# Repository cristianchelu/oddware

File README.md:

# oddware

Personal collection of projects that don't deserve their own repositories.

## Projects

| Path | Description |
|------|-------------|
| [esphome.pet-bowl-monitor/](esphome.pet-bowl-monitor/) | ESPHome cat water bowl monitor — scale, camera, IR, Home Assistant integration |
| [esphome.petkit-eversweet-3-pro/](esphome.petkit-eversweet-3-pro/) | Replacement ESPHome base for the PetKit Eversweet 3 Pro UVC fountain — weighs it, logs every drink to Home Assistant |
| [esphome.petlibro-plwf105/](esphome.petlibro-plwf105/) | ESPHome firmware for the PetLibro Dockstream PLWF105 fountain — gram-calibrated scale, drink logging, one-button device UX |
| [zigbee.cat-toy/](zigbee.cat-toy/) | Zigbee cat toys: flappy bird, flappy fish and rolling ball on one shared board. Scripted KiCad layout |

## Moved out

| Project | New home |
|---------|----------|
| xiaomi-feeder-iv2001 — open firmware for the Xiaomi Smart Pet Food Feeder 2 | moved to [cristianchelu/xiaomi-feeder-iv2001](https://github.com/cristianchelu/xiaomi-feeder-iv2001) |

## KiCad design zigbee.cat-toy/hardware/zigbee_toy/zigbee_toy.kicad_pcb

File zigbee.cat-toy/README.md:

# @oddware/zigbee.cat-toy

One controller board for three battery-powered Zigbee cat toys: a flapping
bird, a flapping fish and a rolling ball. The board drives a motor and a
speaker, wakes on motion, charges over USB-C, and joins Home Assistant as a
sleepy Zigbee end device. The toys differ only in what is plugged into its
three connectors.

> This one is vibe coded: AI agents did most of the work, with me steering.
> It has never been built. There is no expectation that it works or will be
> finished; it's a side project parked here.

## Status

- **Rev A** — nRF52840 (Ebyte E73). Never built: the module and the
  accelerometer are "Standard only" parts at JLC, which put 5 assembled
  boards at about $200. Kept under the `zigbee.cat-toy/rev-a` tag.
- **Rev B** (this tree) — ESP32-C6. Every assembled part is eligible for
  JLC Economic PCBA. DRC-clean, not ordered yet.
- No firmware yet.
- Every fix from the [datasheet review](docs/design_review_rev_b.md) is in
  this tree.

## The toys

| Toy | Motor | Battery | Speaker |
|-----|-------|---------|---------|
| Flappy bird | N20 gearmotor, 6 V winding, 300–400 rpm | 1S LiPo pouch, ~500 mAh | yes |
| Flappy fish | same as bird | same as bird | no |
| Rolling ball | N20 gearmotor, 6 V winding, ~100 rpm | 803040, 1000 mAh | no |

- Any 3.7 V cell with a JST-PH lead works, protected or not. The board has
  its own protection and a reverse-polarity FET; JST-PH pigtails come wired
  both ways.
- Motor and speaker plug in with JST-SH (1 mm, 1 A per pin). Crimp the
  leads or buy SH pigtails.
- Keep the ceramic capacitor across the motor tabs. It suppresses brush noise
  next to a 2.4 GHz radio.
- The module has no antenna of its own. Plug a 2.4 GHz FPC antenna into its
  u.FL socket and stick it to the inside of the toy, away from the motor and
  the cell.

Printed parts for the ball and a bench pod:
[hardware/mech/README.md](hardware/mech/README.md).

## The board

36 × 23 mm, 2 layers, every assembled part on top. Passives are 0402,
bulk capacitors 0603/0805.

| Block | Part | Notes |
|-------|------|-------|
| MCU + radio | Espressif ESP32-C6-MINI-1U-H4 | Zigbee/Thread, BLE, Wi-Fi, u.FL antenna socket. USB Serial/JTAG on the charging port |
| 3.3 V | Richtek RT9080-33 | 2 µA quiescent, 600 mA |
| Motor driver | TI DRV8213 | Current sense on IPROPI, no shunt. Firmware picks the hardware current limit per toy: 1.66 A, 324 mA or 69 mA |
| Accelerometer | MSKSEMI LIS2DW12TR-MS | Wake-on-motion and tap. Not ST's LIS2DW12, see below |
| Charger | TP4054 | 260 mA from USB-C. Charge state goes to the MCU through a 10 k pull-up |
| Cell protection | XySemi XB5353A | Low side, FETs built in |
| Reverse polarity | AO3401A | High side |
| Speaker | AO3400A | Low-side PWM switch |
| Status LED | red 0603 | On a GPIO |
| USB ESD | ST USBLC6-2SC6 | D+/D− clamps, referenced to 3V3: on VBUS, the C6's D+ pull-up would back-feed VBUS while unplugged |
| Button | Alps SKRTLAE010 | Side push. Pairing, and BOOT for flashing |

- Left edge — motor and speaker JST-SH connectors (SMD, assembled), battery
  JST-PH (through-hole, hand-soldered).
- Right edge — USB-C and the side-push button, status LED above the USB-C.
- Top edge — the module, 1 mm from the edge.
- Back — 21 labelled test pads, debug UART among them.

**The accelerometer is not an ST part.** MSKSEMI sells it as
"LIS2DW12TR-MS", but the pinout and register map are its own: WHO_AM_I
reads 0x11 and the registers follow the LIS2DH layout (CTRL_REG1 at 0x20,
OUT_X_L at 0x28, AOI1/CLICK blocks). Use a LIS2DH-style driver. Only INT1
is wired; route both wake and tap to it. Pad 4 is grounded: the pin table
says NC, but the datasheet's connection column says GND in every mode.

Schematic: [PDF](hardware/zigbee_toy/zigbee_toy_schematic.pdf). Datasheet review:
[docs/design_review_rev_b.md](docs/design_review_rev_b.md).

### Pin map

| Module pin | GPIO | Net | Notes |
|---|---|---|---|
| 5 | IO2 | MOT_IPROPI | ADC1_CH2. 0.51 V = current limit reached |
| 6 | IO3 | MOT_IN1 | DRV8213 IN1 |
| 9 | IO4 | MOT_IN2 | DRV8213 IN2 |
| 19 | IO14 | MOT_GAINSEL | drive low / drive high / input (Hi-Z) |
| 10 | IO5 | SPK_PWM | speaker FET gate |
| 12, 13 | IO0, IO1 | XTAL_32K | 32.768 kHz crystal for the light-sleep clock |
| 15 | IO6 | VBAT_SENSE | ADC1_CH6, VBAT / 2 |
| 16 | IO7 | ACC_INT1 | low-power GPIO: wakes from deep sleep too |
| 22 | IO8 | I2C_SDA | 4.7 k pull-up, which also holds the IO8 strap high |
| 24 | IO18 | I2C_SCL | 4.7 k pull-up. Accelerometer at 0x19 |
| 23 | IO9 | BTN | BOOT strap, 10 k pull-up (R5). Hold while resetting for download mode |
| 25 | IO19 | VBUS_SENSE | 0.61 × VBUS: high when plugged in, charging or full |
| 26 | IO20 | CHG_STAT | low while charging, 10 k pull-up (R10) |
| 29 | IO23 | LED_STATUS | high = on |
| 17, 18 | IO12, IO13 | USB D−, D+ | |
| 30, 31 | RXD0, TXD0 | DBG_RX, DBG_TX | test pads, 3.3 V |
| 8 | EN | EN | 10 k / 1 µF power-on delay, test pad |

Unconnected: IO15 (a strapping pin), IO21, IO22.

Motor drive: PWM between drive and brake. Forward IN1 = 1, IN2 = 1 − duty;
reverse IN2 = 1, IN1 = 1 − duty. Both pins need a PWM channel. Drive/coast
also spins the motor, but IPROPI reads zero while coasting, so current
sensing and stall detection stop working. The driver only auto-sleeps with
IN1 = IN2 = 0; brake keeps it awake, so park both inputs low before sleeping.

The JST-SH is rated 1 A per pin. Use the 324 mA limit (GAINSEL Hi-Z) as the
default; at 1.66 A a stalled motor overloads the connector.

### Power

Idle current is about 65 µA, nearly all of it the C6 in Zigbee light sleep
(about 54 µA, a forum figure, not measured here). The regulator, the
protection IC, the accelerometer and the battery divider add a few µA each.
That is 1.6 mAh a day. Ten minutes of flapping costs about 25 mAh, so a
500 mAh bird gets roughly three weeks per charge.

The battery divider is 1 M / 1 M. At that impedance the ADC's own input
current shifts the reading; calibrate it against a meter in firmware.

- Low battery — the XB5353A cuts off at 2.4 V, but the C6 browns out below
  about 3.4 V during radio bursts and reboots in a loop. Stop the radio and
  sleep at 3.4 V; the protection IC is the last line.
- First cell — the XB5353A may start in its off state when a cell is
  connected. Plug in USB once to wake it.
- Charge state — CHG_STAT low = charging; high with VBUS_SENSE high = done;
  high with VBUS_SENSE low = unplugged. With USB plugged in and the radio
  awake, the board draws through the charger, which then stays in its
  constant-voltage float and CHG_STAT stays low. Not an error.
- Charger heat — 0.34 W at 260 mA into a 3.7 V cell. On a warm day the
  TP4054 folds its current back.

### Layout

- **Edge distance:** every assembled part body is at least 1 mm from the
  board edge (see [Ordering](#ordering)). Exempt: the USB-C and the button
  on the right edge, the two JST-SH plugs on the left. The SH fronts sit
  0.5 mm in from the edge so their solder tabs keep 0.3 mm of copper
  clearance. `gen_pcb.py` refuses a placement that breaks the rule.
- **Module position:** 1 mm from the top edge. Under it, two rows of parts
  with a channel between them: crystal, accelerometer and USB protection in
  the first row, regulator and the battery divider in the second.
- **USB-C side:** the channel between the module's right pads and the
  receptacle pads is 2.1 mm wide. Only the two CC pull-downs live in it,
  standing vertical beside their pads. The VBUS divider sits above the
  receptacle, beside the top mounting hole, fed from the upper VBUS pad;
  VBUS_SENSE comes back to pin 25 on the back layer, under the module's
  right pad column.
- **Antenna keepout:** no copper on either layer between the module's top
  pads and the board edge. That is the area under an ESP32-C6-MINI-1's PCB
  antenna, so the MINI-1 fits the same pads. The keepout is a rule area in
  the module footprint, so DRC checks it.
- **USB D+/D−:** each USB-C pad pair is joined on the back layer through
  vias inside the receptacle. D+ passes left of the shell tab, D− right of
  it, into the USBLC6 below the receptacle. From there both run on the back
  layer under the module's bottom edge and come up through vias inside the
  pad ring at pins 17 and 18.
- **Under the USB-C:** no top-layer copper except the pad escapes. On the
  back, only the escape vias and the VBUS run, so the shell still ties into
  the ground pour.
- **Crystal:** no back-layer copper under it or its traces.
- The DSN export turns the last two into keepouts for the autorouter; hand
  routes are not checked against them.
- **Battery corner:** the protection IC body is 1.4 mm from the JST-PH
  housing and 0.7 mm outside the 4 mm circle an M2 screw head covers at
  H2; CELL_P goes round its ground pad on the far side, and the bulk
  capacitor sits to the right of that with its own ground via.
- **VBAT:** back layer from the battery FET up the left column to the
  driver, and along the bottom in a channel between the two rows of test
  pads to the regulator, the battery divider and the charger.
- **3V3:** regulator, 22 µF next to it, 10 µF and 100 nF at module pin 3.
- **Motor driver:** C3's ground pad drops straight onto the thermal pad,
  which has two vias to the back. Keep the back plane under the driver
  whole: with one trace under it, C3's return path was 15 mm long instead
  of 1.
- **Charger:** two ground vias under the TP4054, on its pin 2, which is its
  heat path. The VBAT lane dips below them.
- **Ground:** both layers poured. `gen_pcb.py stitch` adds a 2.5 mm via grid
  and a via to every pour island it can reach. Five of the module's nine
  centre ground pads have a via.

## Flashing

The C6 has USB Serial/JTAG on the charging port: flashing, console and
debugging over one cable.

1. Connect the USB-C to the computer.
2. Flash with ESPHome or esptool. The tool resets the C6 into download mode
   over USB; the button is not needed.

If the firmware has disabled USB or does not respond:

1. Hold the button.
2. Connect the EN test pad to a GND pad for a moment.
3. Release the button. The C6 is in download mode.

UART0 is also on the TX and RX test pads, 3.3 V.

## Rebuilding

The schematic and the board are generated by scripts. Do not edit them in
KiCad; the next build overwrites the changes.

| To change | Edit |
|-----------|------|
| Parts and nets | `hardware/tools/design.py` |
| Board placement | `hardware/tools/placement.py` |
| Copper | `hardware/tools/routes.py` (hand routes), `routes_frozen.py` (a frozen Freerouting pass, hand-edited since) |
| Silkscreen | `hardware/tools/silk.py` |

Needs the KiCad 10 flatpak, ImageMagick, and network access the first time
a new LCSC number shows up in the BOM.

1. Run `hardware/tools/build.sh`. It writes the schematic, runs ERC, checks
   the netlist against intent, and writes the PDF and the JLC BOM.
2. Run `hardware/tools/pcb_build.sh`. It places, adds the copper, stitches,
   adds the silkscreen, runs DRC and checks part spacing
   (`check_spacing.py`: bodies 0.2 mm, pads 0.15 mm apart; the library
   courtyards overlap by their margins). Placement fails if a part breaks the
   edge distance.
3. Run `hardware/tools/export_jlc.sh`. It writes `gerbers.zip`, `cpl.csv`
   and `bom.csv` to `hardware/zigbee_toy/build/jlc/`.

To autoroute nets that have no copper yet (needs the Freerouting flatpak and
a JDK; one pass takes up to 10 minutes):

1. Run `gen_pcb.py layout`, then `gen_pcb.py dsn`.
2. Run `tools/freerouting/Route.java` on `build/zigbee_toy.dsn`.
3. Run `gen_pcb.py ses`, then `freeze_routes.py append`. The new copper
   goes into `routes_frozen.py`.

Run the Python scripts with the flatpak's interpreter
(`flatpak run --command=python3 org.kicad.kicad`). Outputs go to `build/`
folders, which git ignores.

## Ordering

- Order Economic PCBA. Nine parts are JLC "Extended" ($3 each per order):
  module, motor driver, accelerometer, regulator, protection IC, USB ESD,
  USB-C, JST-SH, button. Parts come to about $8.25 a board.
- The order's BOM step decides Economic or Standard, not the "PCBA Type"
  field on the part page. One Standard-only part moves the whole order to
  Standard. Re-check there after any part swap.
- JLC flags the module and the accelerometer for X-ray inspection. Not
  confirmed yet whether that changes the PCBA type.
- Parts sit as close as 1 mm to the edge. JLC panelizes Economic boards
  itself and routes them apart, and its Economic FAQ asks for 0.3 mm. The
  2.5 mm in the general assembly terms is for Standard PCBA, where the
  machines grip the board's own edge.
- The USB-C overhangs the board edge by 1 mm. Say so in the order remark.
- JLC places a part using the origin and rotation of *its* EasyEDA
  footprint, not KiCad's. `jlc_cpl.py` fits each KiCad footprint onto the
  EasyEDA one and corrects the CPL (the module is 0.65 mm off, the USB-C
  1.6 mm); it fails if a fit is poor. Check JLC's 3D placement preview
  anyway. The EasyEDA footprints are cached in `hardware/tools/easyeda/`.
- The FPC antenna is not on the BOM. Any 2.4 GHz FPC antenna with a u.FL
  (IPEX MHF1) lead fits.
- The ESP32-C6-MINI-1 (PCB antenna) drops onto the same pads; its antenna
  overhangs the top edge by 3.1 mm. Swap the LCSC number in `design.py` and
  mention the overhang in the order remark. As of 2026-10 every MINI-1
  listing at JLC is out of stock and Standard only.

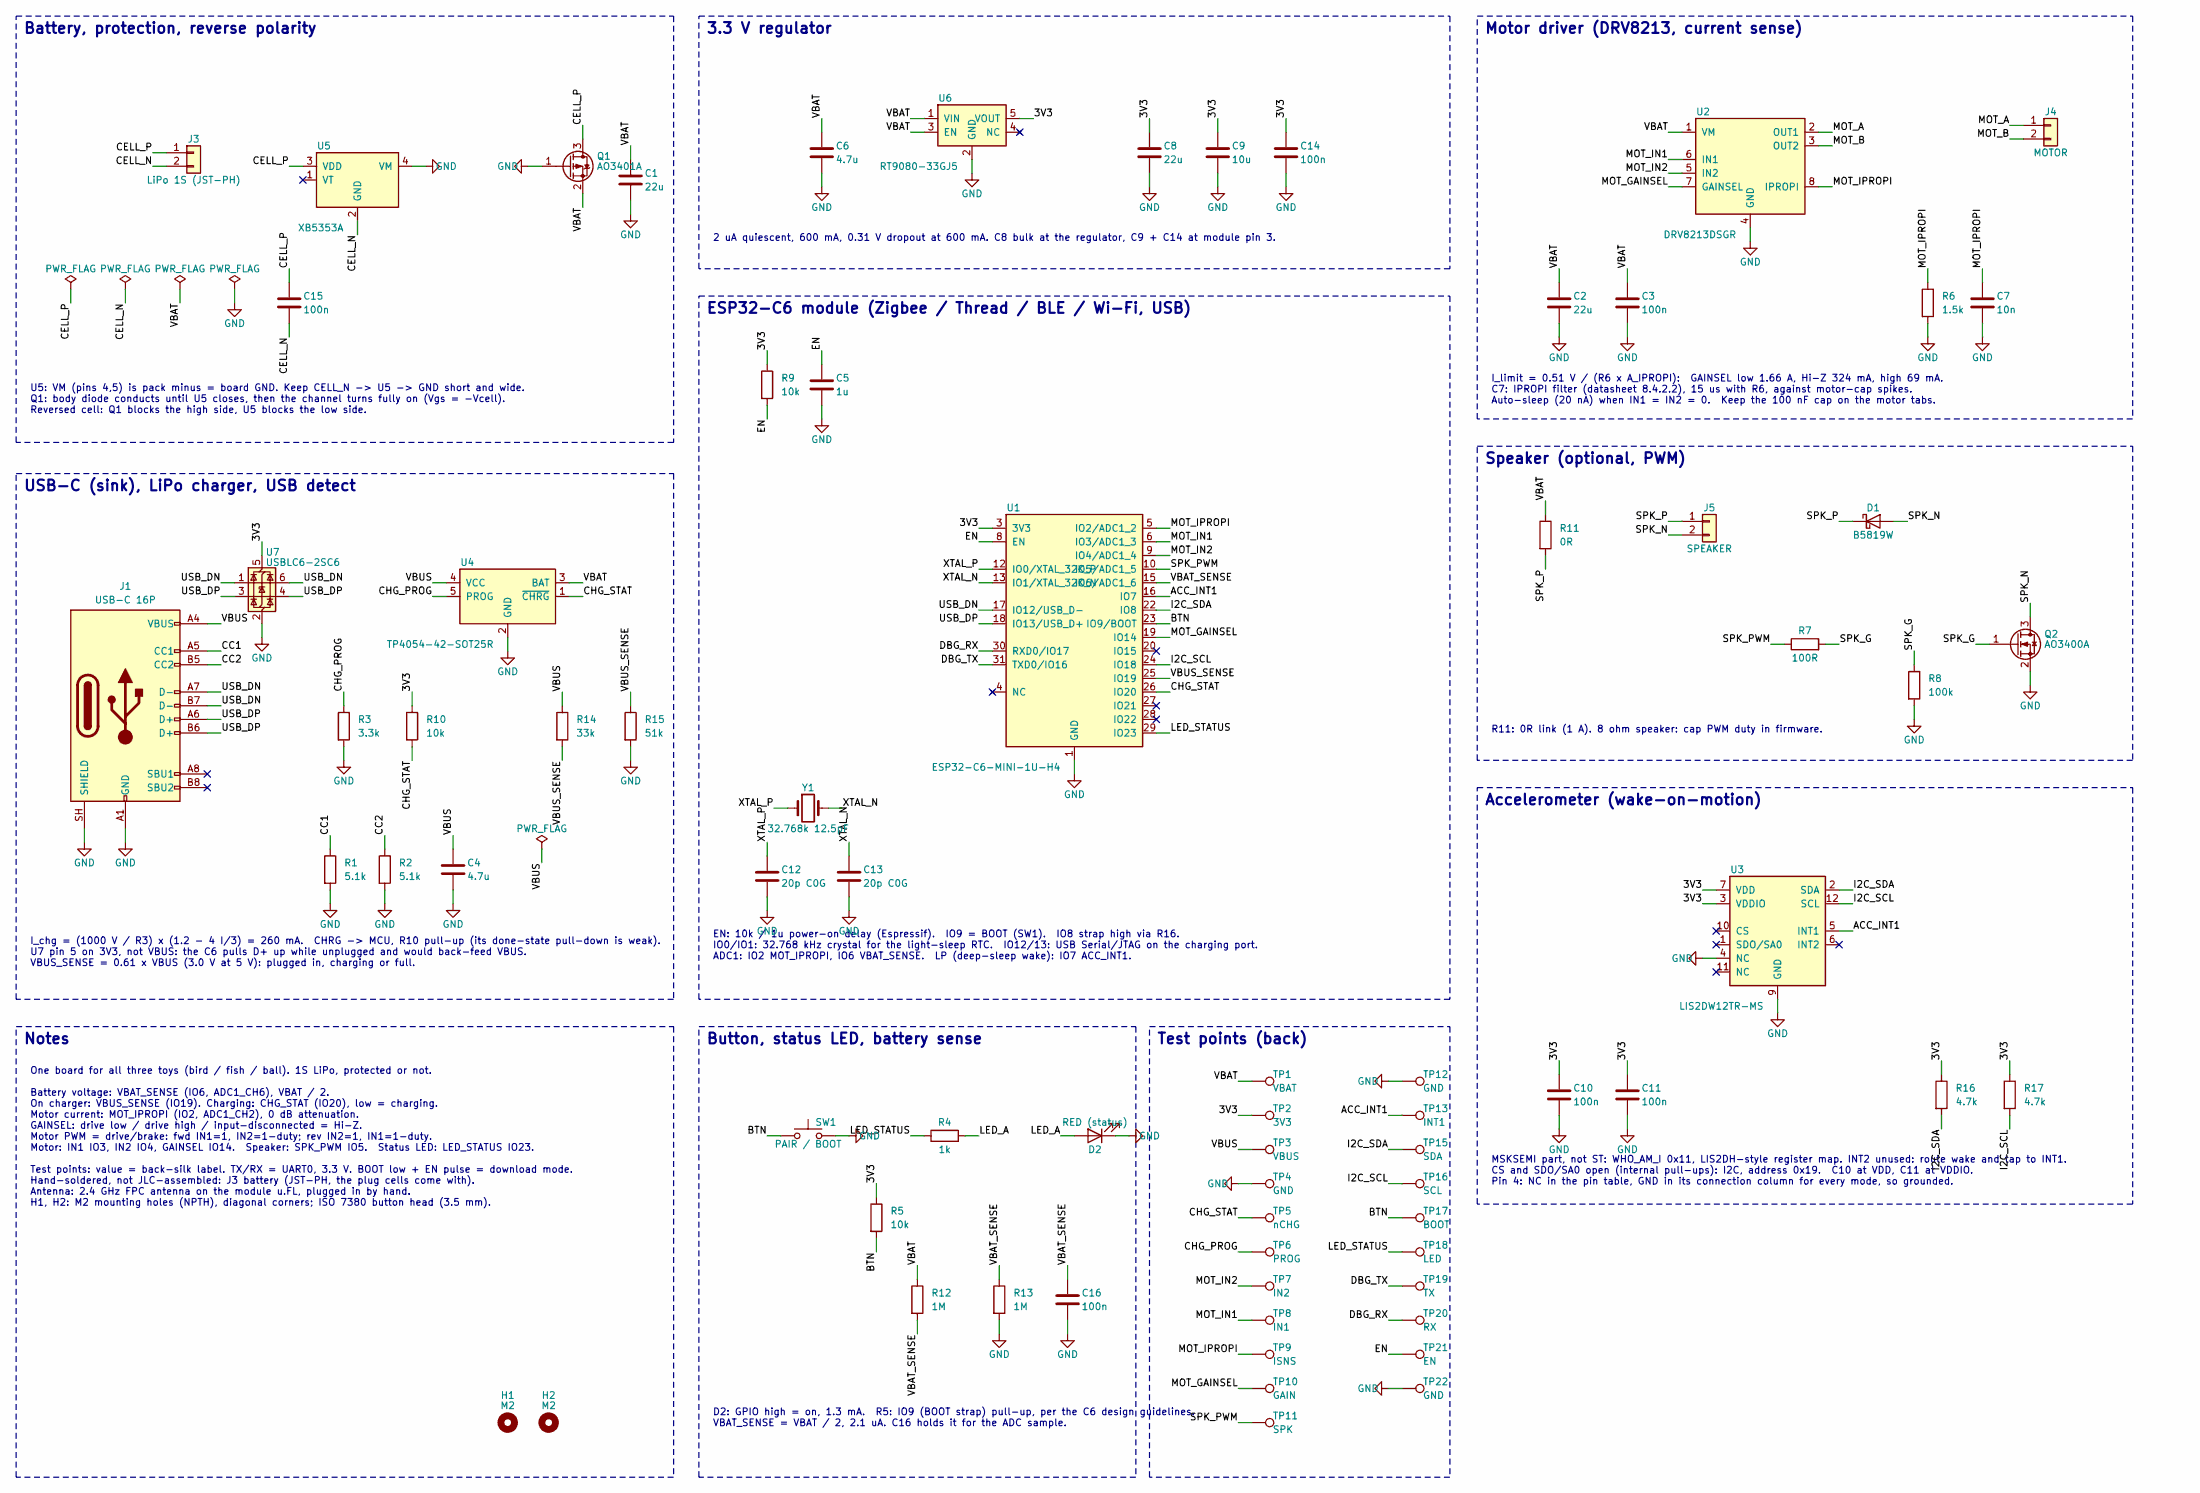
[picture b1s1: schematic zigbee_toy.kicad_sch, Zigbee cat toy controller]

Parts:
C1, C2, C8: 22u; C_0805_2012Metric; LCSC C45783
C3, C10, C11, C14, C15, C16: 100n; C_0402_1005Metric; LCSC C1525
C4, C6: 4.7u; C_0603_1608Metric; LCSC C19666
C5: 1u; C_0402_1005Metric; LCSC C52923
C7: 10n; C_0402_1005Metric; LCSC C15195
C9: 10u; C_0603_1608Metric; LCSC C19702
C12, C13: 20p C0G; C_0402_1005Metric; LCSC C1554
D1: B5819W; D_SOD-123; LCSC C8598
D2: RED (status); LED_0603_1608Metric; LCSC C2286
H1, H2: M2; MountingHole_2.2mm_M2_ISO7380
J1: USB-C 16P; USB_C_Receptacle_HRO_TYPE-C-31-M-12; LCSC C165948
J3: LiPo 1S (JST-PH); JST_PH_S2B-PH-K_1x02_P2.00mm_Horizontal; LCSC C173752
J4: MOTOR; JST_SH_SM02B-SRSS-TB_1x02-1MP_P1.00mm_Horizontal; LCSC C160402
J5: SPEAKER; JST_SH_SM02B-SRSS-TB_1x02-1MP_P1.00mm_Horizontal; LCSC C160402
Q1: AO3401A; SOT-23; LCSC C15127
Q2: AO3400A; SOT-23; LCSC C20917
R1, R2: 5.1k; R_0402_1005Metric; LCSC C25905
R3: 3.3k; R_0402_1005Metric; LCSC C25890
R4: 1k; R_0402_1005Metric; LCSC C11702
R5, R9, R10: 10k; R_0402_1005Metric; LCSC C25744
R6: 1.5k; R_0402_1005Metric; LCSC C25867
R7: 100R; R_0402_1005Metric; LCSC C25076
R8: 100k; R_0402_1005Metric; LCSC C25741
R11: 0R; R_0402_1005Metric; LCSC C17168
R12, R13: 1M; R_0402_1005Metric; LCSC C26083
R14: 33k; R_0402_1005Metric; LCSC C25779
R15: 51k; R_0402_1005Metric; LCSC C25794
R16, R17: 4.7k; R_0402_1005Metric; LCSC C25900
SW1: PAIR / BOOT; SW_Push_1P1T-MP_NO_Horizontal_Alps_SKRTLAE010; LCSC C110293
TP1: VBAT; TestPoint_Pad_D1.0mm
TP2: 3V3; TestPoint_Pad_D1.0mm
TP3: VBUS; TestPoint_Pad_D1.0mm
TP4, TP12, TP22: GND; TestPoint_Pad_D1.0mm
TP5: nCHG; TestPoint_Pad_D1.0mm
TP6: PROG; TestPoint_Pad_D1.0mm
TP7: IN2; TestPoint_Pad_D1.0mm
TP8: IN1; TestPoint_Pad_D1.0mm
TP9: ISNS; TestPoint_Pad_D1.0mm
TP10: GAIN; TestPoint_Pad_D1.0mm
TP11: SPK; TestPoint_Pad_D1.0mm
TP13: INT1; TestPoint_Pad_D1.0mm
TP15: SDA; TestPoint_Pad_D1.0mm
TP16: SCL; TestPoint_Pad_D1.0mm
TP17: BOOT; TestPoint_Pad_D1.0mm
TP18: LED; TestPoint_Pad_D1.0mm
TP19: TX; TestPoint_Pad_D1.0mm
TP20: RX; TestPoint_Pad_D1.0mm
TP21: EN; TestPoint_Pad_D1.0mm
U1: ESP32-C6-MINI-1U-H4; ESP32-C6-MINI-1U; LCSC C20627095
U2: DRV8213DSGR; Texas_DSG0008A_WSON-8-1EP_2x2mm_P0.5mm_EP0.9x1.6mm; LCSC C22407186
U3: LIS2DW12TR-MS; LGA-12_2x2mm_P0.5mm; LCSC C50385411
U4: TP4054-42-SOT25R; SOT-23-5; LCSC C32574
U5: XB5353A; SOT-23-5; LCSC C80628
U6: RT9080-33GJ5; TSOT-23-5; LCSC C841192
U7: USBLC6-2SC6; SOT-23-6; LCSC C7519
Y1: 32.768k 12.5pF; Crystal_SMD_3215-2Pin_3.2x1.5mm; LCSC C32346

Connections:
3V3: C8.1, C9.1, C10.1, C11.1, C14.1, R5.1, R9.1, R10.1, R16.1, R17.1, TP2.1, U1.3 (3V3), U3.3 (VDDIO), U3.7 (VDD), U6.5 (VOUT), U7.5 (VBUS)
ACC_INT1: TP13.1, U1.16 (IO7), U3.5 (INT1)
BTN: R5.2, SW1.1, TP17.1, U1.23 (IO9/BOOT)
CC1: J1.A5 (CC1), R1.1
CC2: J1.B5 (CC2), R2.1
CELL_N: C15.2, J3.2, U5.2 (GND)
CELL_P: C15.1, J3.1, Q1.3 (D), U5.3 (VDD)
CHG_PROG: R3.1, TP6.1, U4.5 (PROG)
CHG_STAT: R10.2, TP5.1, U1.26 (IO20), U4.1 (~CHRG)
DBG_RX: TP20.1, U1.30 (RXD0/IO17)
DBG_TX: TP19.1, U1.31 (TXD0/IO16)
EN: C5.1, R9.2, TP21.1, U1.8 (EN)
GND: C1.2, C2.2, C3.2, C4.2, C5.2, C6.2, C7.2, C8.2, C9.2, C10.2, C11.2, C12.2, C13.2, C14.2, C16.2, D2.1 (K), J1.A1 (GND), J1.A12 (GND), J1.B1 (GND), J1.B12 (GND), J1.SH (SHIELD), Q1.1 (G), Q2.2 (S), R1.2, R2.2, R3.2, R6.2, R8.2, R13.2, R15.2, SW1.2, TP4.1, TP12.1, TP22.1, U1.1 (GND), U1.2 (GND), U1.11 (GND), U1.14 (GND), U1.36 (GND), U1.37 (GND), U1.38 (GND), U1.39 (GND), U1.40 (GND), U1.41 (GND), U1.42 (GND), U1.43 (GND), U1.44 (GND), U1.45 (GND), U1.46 (GND), U1.47 (GND), U1.48 (GND), U1.49 (GND), U1.50 (GND), U1.51 (GND), U1.52 (GND), U1.53 (GND), U2.4 (GND), U2.9 (EP), U3.4 (NC), U3.8 (GNDIO), U3.9 (GND), U4.2 (GND), U5.4 (VM), U5.5 (VM), U6.2 (GND), U7.2 (GND)
I2C_SCL: R17.2, TP16.1, U1.24 (IO18), U3.12 (SCL)
I2C_SDA: R16.2, TP15.1, U1.22 (IO8), U3.2 (SDA)
LED_A: D2.2 (A), R4.2
LED_STATUS: R4.1, TP18.1, U1.29 (IO23)
MOT_A: J4.1, U2.2 (OUT1)
MOT_B: J4.2, U2.3 (OUT2)
MOT_GAINSEL: TP10.1, U1.19 (IO14), U2.7 (GAINSEL)
MOT_IN1: TP8.1, U1.6 (IO3/ADC1_3), U2.6 (IN1)
MOT_IN2: TP7.1, U1.9 (IO4/ADC1_4), U2.5 (IN2)
MOT_IPROPI: C7.1, R6.1, TP9.1, U1.5 (IO2/ADC1_2), U2.8 (IPROPI)
SPK_G: Q2.1 (G), R7.2, R8.1
SPK_N: D1.2 (A), J5.2, Q2.3 (D)
SPK_P: D1.1 (K), J5.1, R11.2
SPK_PWM: R7.1, TP11.1, U1.10 (IO5/ADC1_5)
USB_DN: J1.A7 (D-), J1.B7 (D-), U1.17 (IO12/USB_D-), U7.1 (I/O1), U7.6 (I/O1)
USB_DP: J1.A6 (D+), J1.B6 (D+), U1.18 (IO13/USB_D+), U7.3 (I/O2), U7.4 (I/O2)
VBAT: C1.1, C2.1, C3.1, C6.1, Q1.2 (S), R11.1, R12.1, TP1.1, U2.1 (VM), U4.3 (BAT), U6.1 (VIN), U6.3 (EN)
VBAT_SENSE: C16.1, R12.2, R13.1, U1.15 (IO6/ADC1_6)
VBUS: C4.1, J1.A4 (VBUS), J1.A9 (VBUS), J1.B4 (VBUS), J1.B9 (VBUS), R14.1, TP3.1, U4.4 (VCC)
VBUS_SENSE: R14.2, R15.1, U1.25 (IO19)
XTAL_N: C13.1, U1.13 (IO1/XTAL_32K_N), Y1.2
XTAL_P: C12.1, U1.12 (IO0/XTAL_32K_P), Y1.1

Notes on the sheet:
Battery, protection, reverse polarity
U5: VM (pins 4,5) is pack minus = board GND. Keep CELL_N -> U5 -> GND short and wide. Q1: body diode conducts until U5 closes, then the channel turns fully on (Vgs = -Vcell). Reversed cell: Q1 blocks the high side, U5 blocks the low side.
USB-C (sink), LiPo charger, USB detect
I_chg = (1000 V / R3) x (1.2 - 4 I/3) = 260 mA. CHRG -> MCU, R10 pull-up (its done-state pull-down is weak). U7 pin 5 on 3V3, not VBUS: the C6 pulls D+ up while unplugged and would back-feed VBUS. VBUS_SENSE = 0.61 x VBUS (3.0 V at 5 V): plugged in, charging or full.
3.3 V regulator
2 uA quiescent, 600 mA, 0.31 V dropout at 600 mA. C8 bulk at the regulator, C9 + C14 at module pin 3.
ESP32-C6 module (Zigbee / Thread / BLE / Wi-Fi, USB)
EN: 10k / 1u power-on delay (Espressif). IO9 = BOOT (SW1). IO8 strap high via R16. IO0/IO1: 32.768 kHz crystal for the light-sleep RTC. IO12/13: USB Serial/JTAG on the charging port. ADC1: IO2 MOT_IPROPI, IO6 VBAT_SENSE. LP (deep-sleep wake): IO7 ACC_INT1.
Button, status LED, battery sense
D2: GPIO high = on, 1.3 mA. R5: IO9 (BOOT strap) pull-up, per the C6 design guidelines. VBAT_SENSE = VBAT / 2, 2.1 uA. C16 holds it for the ADC sample.
Motor driver (DRV8213, current sense)
I_limit = 0.51 V / (R6 x A_IPROPI): GAINSEL low 1.66 A, Hi-Z 324 mA, high 69 mA. C7: IPROPI filter (datasheet 8.4.2.2), 15 us with R6, against motor-cap spikes. Auto-sleep (20 nA) when IN1 = IN2 = 0. Keep the 100 nF cap on the motor tabs.
Speaker (optional, PWM)
R11: 0R link (1 A). 8 ohm speaker: cap PWM duty in firmware.
Accelerometer (wake-on-motion)
MSKSEMI part, not ST: WHO_AM_I 0x11, LIS2DH-style register map. INT2 unused: route wake and tap to INT1. CS and SDO/SA0 open (internal pull-ups): I2C, address 0x19. C10 at VDD, C11 at VDDIO. Pin 4: NC in the pin table, GND in its connection column for every mode, so grounded.
Test points (back)
Notes
One board for all three toys (bird / fish / ball). 1S LiPo, protected or not. Battery voltage: VBAT_SENSE (IO6, ADC1_CH6), VBAT / 2. On charger: VBUS_SENSE (IO19). Charging: CHG_STAT (IO20), low = charging. Motor current: MOT_IPROPI (IO2, ADC1_CH2), 0 dB attenuation. GAINSEL: drive low / drive high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

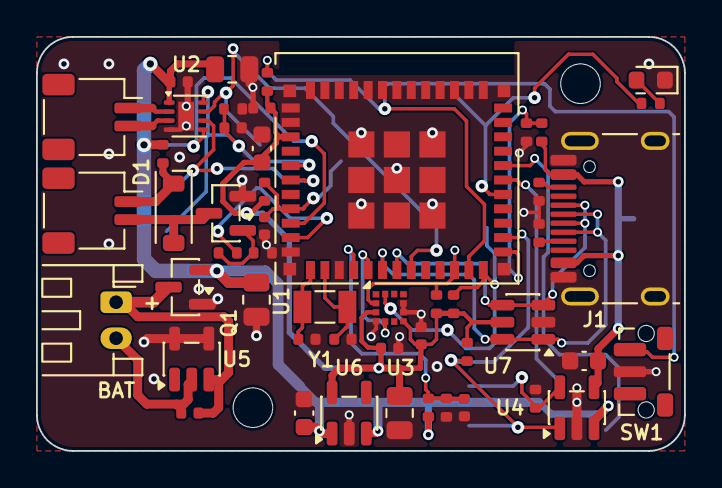
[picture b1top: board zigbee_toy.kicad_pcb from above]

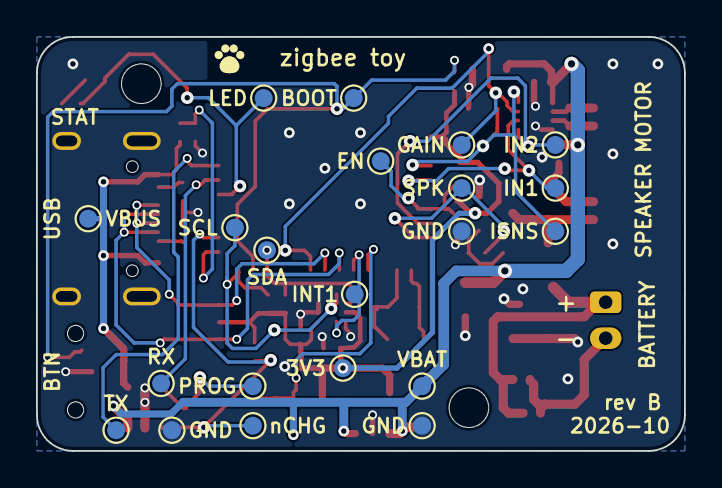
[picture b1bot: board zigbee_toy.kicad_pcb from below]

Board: 2 copper layers, 36.0 x 23.0 mm, 73 parts (21 on the bottom side), 35 nets.

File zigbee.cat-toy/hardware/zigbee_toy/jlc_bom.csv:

"Comment","Qty","Designator","Footprint","LCSC Part #"
"22u","3","C1,C2,C8","Capacitor_SMD:C_0805_2012Metric","C45783"
"100n","6","C3,C10,C11,C14,C15,C16","Capacitor_SMD:C_0402_1005Metric","C1525"
"4.7u","2","C4,C6","Capacitor_SMD:C_0603_1608Metric","C19666"
"1u","1","C5","Capacitor_SMD:C_0402_1005Metric","C52923"
"10n","1","C7","Capacitor_SMD:C_0402_1005Metric","C15195"
"10u","1","C9","Capacitor_SMD:C_0603_1608Metric","C19702"
"20p C0G","2","C12,C13","Capacitor_SMD:C_0402_1005Metric","C1554"
"B5819W","1","D1","Diode_SMD:D_SOD-123","C8598"
"RED (status)","1","D2","LED_SMD:LED_0603_1608Metric","C2286"
"USB-C 16P","1","J1","Connector_USB:USB_C_Receptacle_HRO_TYPE-C-31-M-12","C165948"
"MOTOR","1","J4","Connector_JST:JST_SH_SM02B-SRSS-TB_1x02-1MP_P1.00mm_Horizontal","C160402"
"SPEAKER","1","J5","Connector_JST:JST_SH_SM02B-SRSS-TB_1x02-1MP_P1.00mm_Horizontal","C160402"
"AO3401A","1","Q1","Package_TO_SOT_SMD:SOT-23","C15127"
"AO3400A","1","Q2","Package_TO_SOT_SMD:SOT-23","C20917"
"5.1k","2","R1,R2","Resistor_SMD:R_0402_1005Metric","C25905"
"3.3k","1","R3","Resistor_SMD:R_0402_1005Metric","C25890"
"1k","1","R4","Resistor_SMD:R_0402_1005Metric","C11702"
"10k","3","R5,R9,R10","Resistor_SMD:R_0402_1005Metric","C25744"
"1.5k","1","R6","Resistor_SMD:R_0402_1005Metric","C25867"
"100R","1","R7","Resistor_SMD:R_0402_1005Metric","C25076"
"100k","1","R8","Resistor_SMD:R_0402_1005Metric","C25741"
"0R","1","R11","Resistor_SMD:R_0402_1005Metric","C17168"
"1M","2","R12,R13","Resistor_SMD:R_0402_1005Metric","C26083"
"33k","1","R14","Resistor_SMD:R_0402_1005Metric","C25779"
"51k","1","R15","Resistor_SMD:R_0402_1005Metric","C25794"
"4.7k","2","R16,R17","Resistor_SMD:R_0402_1005Metric","C25900"
"PAIR / BOOT","1","SW1","Button_Switch_SMD:SW_Push_1P1T-MP_NO_Horizontal_Alps_SKRTLAE010","C110293"
"ESP32-C6-MINI-1U-H4","1","U1","zigbee_toy:ESP32-C6-MINI-1U","C20627095"
"DRV8213DSGR","1","U2","Package_SON:Texas_DSG0008A_WSON-8-1EP_2x2mm_P0.5mm_EP0.9x1.6mm","C22407186"
"LIS2DW12TR-MS","1","U3","Package_LGA:LGA-12_2x2mm_P0.5mm","C50385411"
"TP4054-42-SOT25R","1","U4","Package_TO_SOT_SMD:SOT-23-5","C32574"
"XB5353A","1","U5","Package_TO_SOT_SMD:SOT-23-5","C80628"
"RT9080-33GJ5","1","U6","Package_TO_SOT_SMD:TSOT-23-5","C841192"
"USBLC6-2SC6","1","U7","Package_TO_SOT_SMD:SOT-23-6","C7519"
"32.768k 12.5pF","1","Y1","Crystal:Crystal_SMD_3215-2Pin_3.2x1.5mm","C32346"

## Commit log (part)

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2026-06-07 Add initial project structure and documentation for Xiaomi Smart Pet Food Feeder 2 firmware
2026-06-07 xiaomi.feeder.iv2001: add architecture specs
2026-06-07 xiaomi.feeder.iv2001: bootstrap
2026-06-07 xiaomi.feeder.iv2001: adopt LinkIt SDK build bridge for MT7682
    Replace Airoha/AW7698 references with LinkIt v4.6.2 (mt7682_hdk, no PSRAM).
    Add build-env app bridge, iv2001 board wiring, W25Q16DW flash patch,
    IV2001 flash_download.cfg, and OTA foundation plan/spec updates.
    No application C code yet — Step 1 scaffold follows.
2026-06-07 xiaomi.feeder.iv2001: bootloader and minimal app
2026-06-07 xiaomi.feeder.iv2001: A/B boot selector in bootloader
2026-06-07 xiaomi.feeder.iv2001: WiFi STA + NVDM
2026-06-07 xiaomi.feeder.iv2001: add flash tool harness
2026-06-07 xiaomi.feeder.iv2001: MQTT + LWT
2026-06-08 xiaomi.feeder.iv2001: OTA via MQTT
2026-06-08 xiaomi.feeder.iv2001: add minimal AP provisioning.
2026-06-08 xiaomi.feeder.iv2001: improve fallback ap behavior
2026-06-09 xiaomi.iv.2001: display driver MVP
2026-06-10 xiaomi.feeder.iv2001: clean sdk before build
2026-06-10 xiaomi.feeder.iv2001: re-fix display boot selftest after sdk clean
2026-06-10 xiaomi.feeder.iv2001: WFCI bus arbitration
2026-06-10 xiaomi.feeder.iv2001: display presentation abstraction
2026-06-10 xiaomi.feeder.iv2001: Implement MQTT and Wi-Fi indicators for display feedback
    - Added `display_mqtt_indicator` and `display_wifi_indicator` modules to manage visual feedback for MQTT and Wi-Fi connection states.
    - Updated `AGENTS.md` to clarify the process for maintaining Tier 2 stories alongside Tier 3 specs.
    - Enhanced `Makefile` to include new indicator source files.
    - Introduced new functions for MQTT and Wi-Fi connection states, including connecting, connected, and error states.
    - Updated relevant specs to document the behavior of the new indicators and their integration into the provisioning and MQTT processes.
    - Added unit tests for the new display indicators to ensure correct functi
2026-06-10 xiaomi.feeder.iv2001: weigh sensor driver
2026-06-10 xiaomi.feeder.iv2001: add minimal app task
2026-06-10 xiaomi.feeder.iv2001: initial button HAL
2026-06-10 xiaomi.feeder.iv2001: add button gesture FSM on debounced edges
    Introduce button_gesture (short/long/combo) over DOWN/UP transitions from
    button_input, fix P1.0 dispense active-high polarity, and stub UART lines
    until dispense/sleep/provision actions are wired.
2026-06-10 xiaomi.feeder.iv2001: hopper IR bringup WIP
2026-06-10 xiaomi.feeder.iv2001: agent nudge to build before claiming green
2026-06-11 xiaomi.feeder.iv2001: motor control HAL
2026-06-11 xiaomi.feeder.iv2001: add ADC driver
2026-06-11 xiaomi.feeder.iv2001: OTA fix
2026-06-11 xiaomi.feeder.iv2001: adc calibration and reading
2026-06-11 xiaomi.feeder.iv2001: dispense task
2026-06-11 xiaomi.feeder.iv2001: Implement application logging framework
    - Introduced `app_log` module for unified logging across the application, replacing syslog.
    - Added logging levels: debug, info, warn, and error, configurable via `APP_LOG_LEVEL`.
    - Updated various components (MQTT and Wi-Fi adapters) to utilize the new logging system.
    - Enhanced logging for connection milestones and error handling.
    - Added tests for logging functionality to ensure correct behavior and output format.
    - Updated documentation to reflect changes in logging practices.
2026-06-11 xiaomi.feeder.iv2001: logger refactor
2026-06-11 xiaomi.feeder.iv2001: revert wifi log silencing
2026-06-11 xiaomi.feeder.iv2001: refactor OTA logs.
2026-06-11 xiaomi.feeder.iv2001: motor cli commands nonblocking
2026-06-11 xiaomi.feeder.iv2001: telnet
2026-06-11 xiaomi.feeder.iv2001: ota memory reclaim
2026-06-13 fix: WiFi/MQTT reliability after OTA bank swap
    MQTT subscribe fix:
    - Guard MQTTYield while connect worker owns the socket — prevents
    select/recv race that caused subscribe timeouts and session flapping
    - SDK patch: short-poll select (200 ms) in mqtt_read to work around
    LwIP rcvevent race on MT7682
    - Increase mqtt_cn worker stack 3072 → 4096 B
2026-06-15 xiaomi.feeder.iv2001: refactor wifi stack per SDK ref
2026-06-15 xiaomi.feeder.iv2001: Implement dispense functionality with CLI support
    - Added dispense command handling in the CLI, allowing users to request dispensing of portions.
    - Introduced a dispense supervisor to manage dispense jobs, including handling motor control and job completion.
    - Updated event handling to include EVT_DISPENSE_REQUEST for initiating dispense jobs.
    - Enhanced display indicators to reflect dispensing status.
    - Added tests for dispense functionality, ensuring correct operation and error handling.
    - Updated documentation to reflect new dispense features and CLI commands.
2026-06-15 xiaomi.feeder.iv2001: migrate firmware build to Airoha IoT SDK 4.7.1
    Switch fetch/tooling from linkit-sdk-v4.6.2-houndify to demoMT v4.7.1,
    rebase SDK patches, fix IV2001 UART pinmux for bootloader bring-up, and
    update build/docs references for the new SDK layout.
2026-06-15 xiaomi.feeder.iv2001: fix OTA preflight heap and bank-B Wi-Fi connect
    Suspend app_cli and wifi_sta during OTA to reclaim stack RAM, raise FreeRTOS
    heap to 192 KB, and wait on PORT_SECURE/DHCP semaphores so bank-B boots
    (~38 s connect) no longer fail the 30 s link-status poll timeout.
2026-06-15 xiaomi.feeder.iv2001: add debounced mains sense on AW9523B P1.1
    Bench probe corrected P1.1 polarity (low = mains). Introduce power_source_port,
    debounced power_source_input, and power show CLI as the foundation for the
    power FSM and MQTT source reporting.
2026-06-15 xiaomi.feeder.iv2001: add HA dispense MVP with mqtt outbox publish path.
    Queue post-connect MQTT TX through mqtt_io, publish HA button discovery
    on a plain connection topic for availability, and wire cmd/dispense to the
    dispense supervisor so Home Assistant can trigger feeds without socket races.
2026-06-16 xiaomi.feeder.iv2001: unify MQTT ingress and dispense lifecycle logging.
    Centralize handled MQTT command lines in app_mqtt_dispatch and source-agnostic
    dispense started/busy logs in the supervisor so UART and HA share one format.
2026-06-16 xiaomi.feeder.iv2001: use retail HA device manufacturer and model.
    HA discovery now reports Xiaomi Smart Pet Food Feeder 2 to match the physical
    hardware; spec and AGENTS carve out this as the allowed branding exception.
2026-06-16 xiaomi.feeder.iv2001: telnet session fixes
2026-06-16 xiaomi.feeder.iv2001: update README
2026-06-16 Document bank-B Wi-Fi boot delay and fix STA connect order.
    Bench shows ~30 s N9 idle on any bank-B boot (not OTA-specific); CM4
    mitigations including credential-before-radio order do not remove it.
    Split wifi_port into set_credentials/arm_connect, reorder
    wifi_session_connect per SDK, and add wifi_boot_policy for bank-aware
    wait_ready timeout. Canonical spec: wifi-lifecycle § Bank-B boot delay.
2026-06-16 Wire manual dispense button and child lock from physical controls.
    Persist child lock in NVDM, submit one portion on dispense short press,
    and show blank-screen lock icon blink when blocked without disturbing
    weight updates or Wi-Fi/MQTT indicators.
2026-06-16 Harden child lock combo timing and block all physical gestures when locked.
    Combo anchor counts from the first button press, combo-session suppresses
    leaked reset/dispense gestures so lock-on does not flash blocked feedback,
    and specs/tests cover staggered press variants and full button blocking.
2026-06-16 Add bowl-error display, MQTT state, and HA discovery slice.
    Panel, UART, and retained petfeeder/<id>/state bowl_error stay in sync.
    Presence and bank move to connection and ota/status; fix MQTT outbox
    publish after connect. Includes mqtt-bench tooling and spec updates.
2026-06-17 xiaomi.feeder.iv2001: mqtt bowl weight sensor
2026-06-17 xiaomi.feeder.iv2001: fix mqtt outbox when OTA active
2026-06-17 xiaomi.feeder.iv2001: OTA animation
2026-06-17 xiaomi.feeder.iv2001: document help `?` cli command
2026-06-18 xiaomi.feeder.iv2001: bootloader healthcheck and rollback
2026-06-26 xiaomi.feeder.iv2001: auto-tare on idle
2026-06-28 esphome.pet-bowl-monitor: initial commit
